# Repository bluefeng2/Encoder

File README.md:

# Magnetic Encoder

## Overview
This project is a custom magnetic encoder designed to act as a drop-in replacement for the CTRE CANCoder.  
The goal was to swap the encoder in without redesigning mounts or assemblies.

The encoder uses the AS5048A magnetic encoder IC and outputs PWM, making it easy to integrate with the roboRIO.

---

## Component Selection
- AS5048A magnetic encoder IC
  - High-resolution rotation sensing
  - Built-in PWM output
- PWM was chosen over SPI or CAN:
  - roboRIO has limited SPI ports
  - Long SPI wires are unreliable
  - CAN has complex circurity
  - CAN requires custom low-level code (Maybe next time)

---

## Case CAD
The bottom case was designed to closely match the CANCoder’s geometry.

- Two mounting holes match the CANCoder
- PCB is retained using snap-in clips

---

## PCB Schematic

---

## PCB Layout

---

## Case + PCB Assembly

---

## BOM

| Item | Quantity | Unit Cost (CAD) | Total Cost (CAD) | Supplier | Link |
|------|----------|-----------------|------------------|----------|------|
| Molex SL Connector (70553-0002) | 3 | 1.34 | 13.58 | Digi-Key | https://www.digikey.ca/en/products/detail/molex/0705530002/114955 |
| Custom PCB | 1 | 23.24 | 23.24 | JLCPCB | — |
| Diametric Cylinder Magnet (5 mm × 12 mm) | 8 | 1.25 | 22.76 | Magnet Montreal | https://magnetmontreal.com/neodymium-cylinder-magnets/cylinder-diametric-magnet-5mm-wide-x-12mm-high-0.2-x-0.47.html |
| Total:| — | — | — | 59.58 CAD | 43.16  USD |

*Total cost includes shipping

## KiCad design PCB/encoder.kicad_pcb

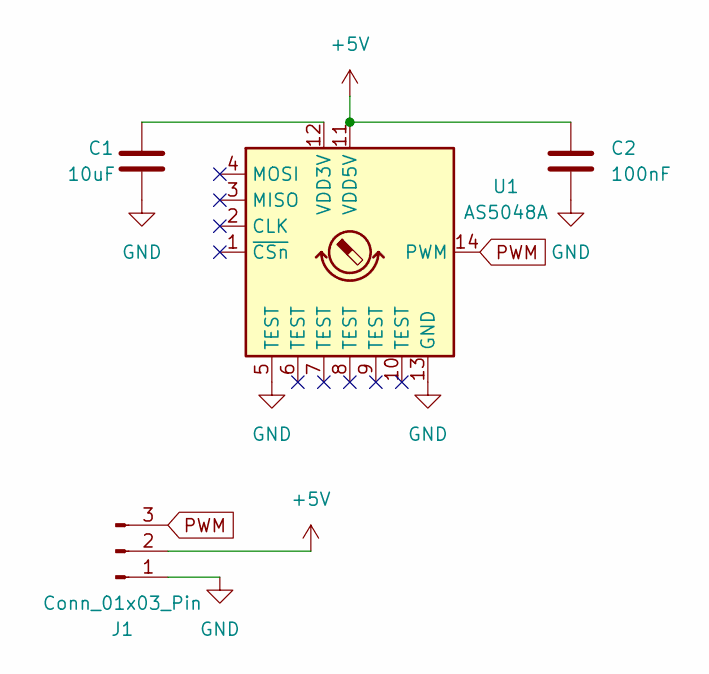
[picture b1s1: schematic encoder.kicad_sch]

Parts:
C1: 10uF; C_0603_1608Metric
C2: 100nF; C_0603_1608Metric
J1: Conn_01x03_Pin; CONN_70553-xxxx_03_MOL
U1: AS5048A; TSSOP-14_4.4x5mm_P0.65mm

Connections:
+5V: C2.1, J1.2, U1.11 (VDD5V)
GND: C1.1, C2.2, J1.1, U1.5 (TEST), U1.13 (GND)
unnamed: C1.2, U1.12 (VDD3V)
PWM: J1.3, U1.14 (PWM)

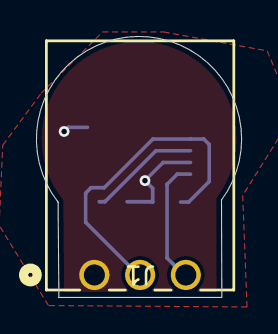
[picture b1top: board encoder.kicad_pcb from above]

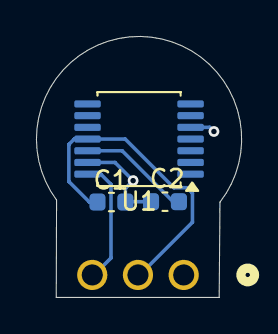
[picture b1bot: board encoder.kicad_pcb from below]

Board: 2 copper layers, 11.4 x 14.5 mm, 4 parts (3 on the bottom side), 4 nets.

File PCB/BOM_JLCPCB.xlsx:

Comment | Designator | Footprint
100nF | C2 | C_0603_1608Metric
AS5048A | U1 | TSSOP-14_4.4x5mm_P0.65mm
10uF | C1 | C_0603_1608Metric

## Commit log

2026-01-04 upload
2026-01-04 Update total costs and magnet price in README
2026-01-05 Reduced count
2026-01-05 Update BOM.csv with new quantities and totals
